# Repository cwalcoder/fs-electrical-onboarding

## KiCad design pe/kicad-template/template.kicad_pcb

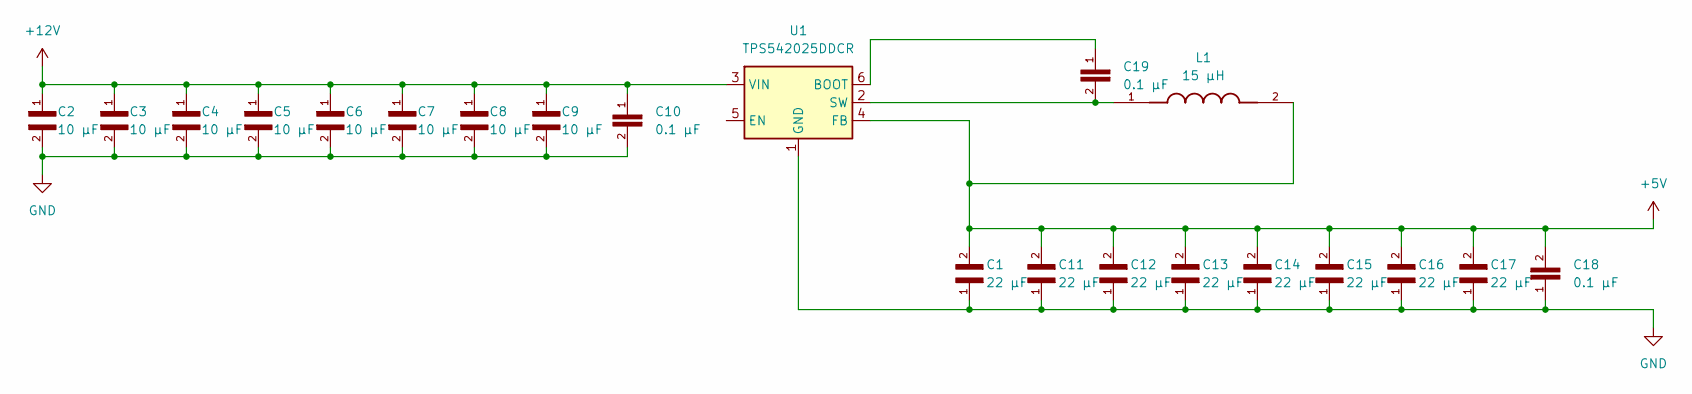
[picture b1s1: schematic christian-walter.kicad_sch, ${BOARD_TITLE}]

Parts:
C1, C11, C12, C13, C14, C15, C16, C17: 22 µF; CAPC1608X87N; PARTREV Jul. 2024; Digikey Part Number 490-13243-2-ND
C2, C3, C4, C5, C6, C7, C8, C9: 10 µF; CAPC1709X100N; Manufacturer Part Number TMK107BBJ106MA-T; Digikey Part Number 587-6023-2-ND
C10, C18, C19: 0.1 µF; CAPC1608X90; Manufacturer Part Number C0603C104K5RACTU; Digikey Part Number 399-C0603C104K5RACTUTR-ND
L1: 15 µH; IND_ETQ-P5M470YFK; PARTREV 0; Digikey Part Number 308-0640CDMCCDS-150MCTR-ND
U1: TPS542025DDCR; SOT-23-6; Manufacturer Part Number TPS542025DDCR; Digikey Part Number 296-TPS542025DDCRCT-ND

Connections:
+5V: C1.2, C11.2, C12.2, C13.2, C14.2, C15.2, C16.2, C17.2, C18.2, L1.2, U1.4 (FB)
+12V: C2.1, C3.1, C4.1, C5.1, C6.1, C7.1, C8.1, C9.1, C10.1, U1.3 (VIN)
GND: C1.1, C2.2, C3.2, C4.2, C5.2, C6.2, C7.2, C8.2, C9.2, C10.2, C11.1, C12.1, C13.1, C14.1, C15.1, C16.1, C17.1, C18.1, U1.1 (GND)
unnamed: C19.1, U1.6 (BOOT)
unnamed: C19.2, L1.1, U1.2 (SW)

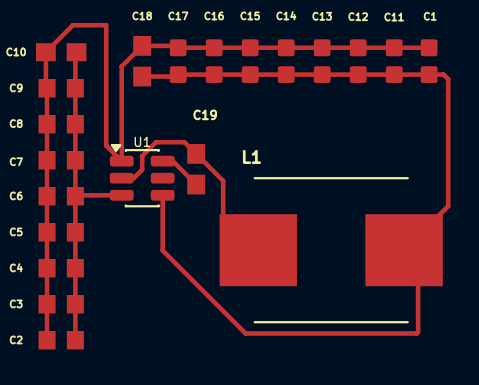
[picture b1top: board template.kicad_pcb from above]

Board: 2 copper layers, 21 parts (0 on the bottom side), 5 nets.
